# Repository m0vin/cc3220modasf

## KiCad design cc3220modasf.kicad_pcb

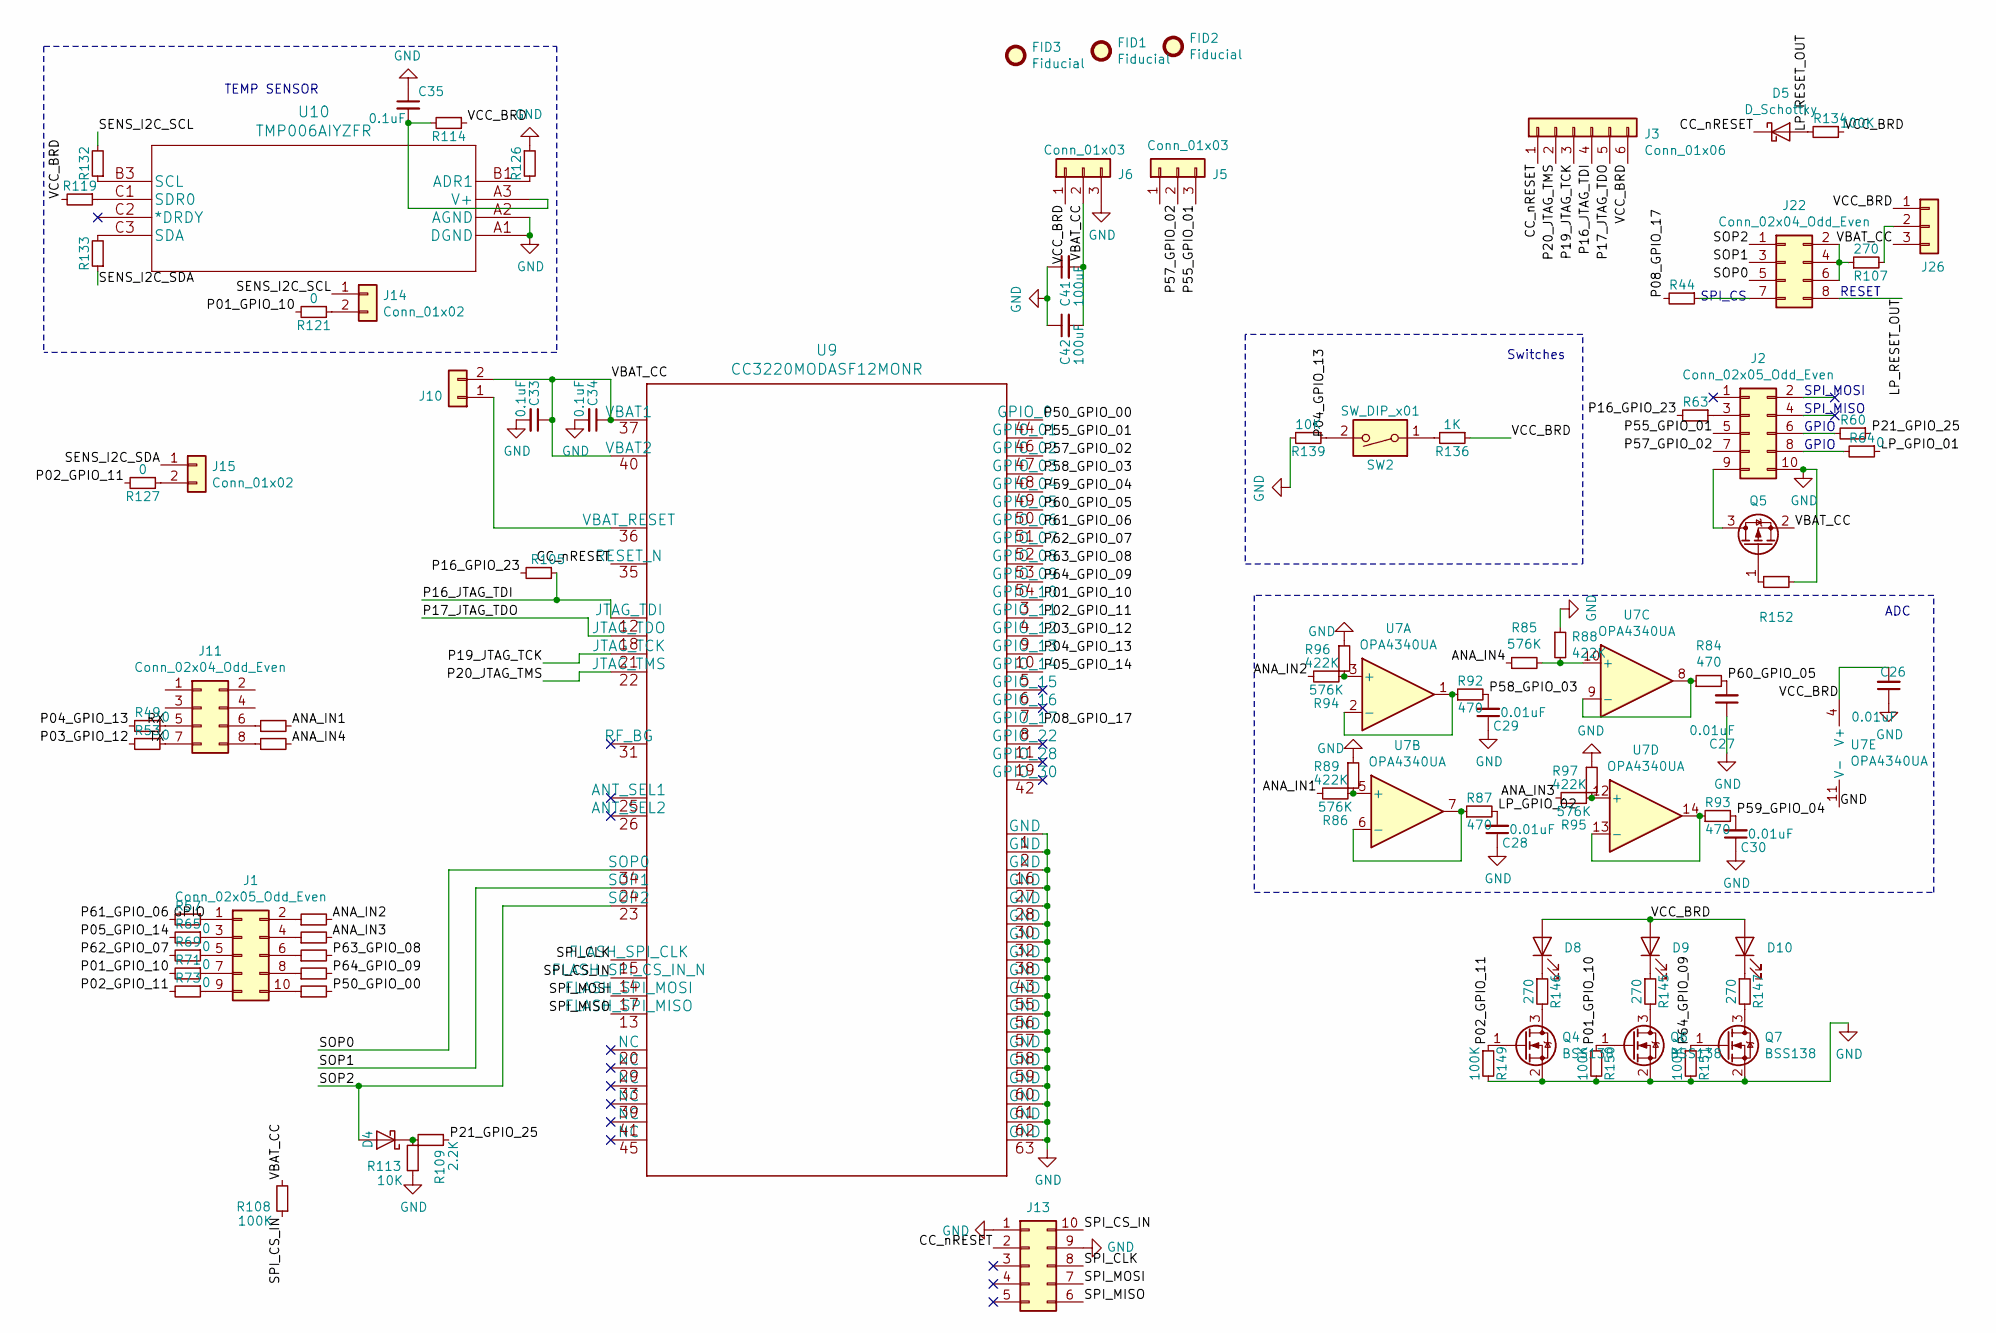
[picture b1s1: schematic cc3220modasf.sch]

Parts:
C26: 0.01uF; C_0402_1005Metric; MFG Part Num GRM155R61A103KA01D
C27, C28, C29, C30: 0.01uF; C_0402_1005Metric; MFG Part Num C1005X7R1C103K
C33, C34, C35: 0.1uF; C_0402_1005Metric; MFG Part Num GRM155R61A104KA01D
C41, C42: 100uF; C_1206_3216Metric; MFG Part Num GRM31CR60J107ME39L
D4, D5: D_Schottky; D_0603_1608Metric; MFG Part Num CD0603-B00340
D8: LED; LED_0603_1608Metric; MFG Part Num SML-LX0603GW-TR
D9: LED; LED_0603_1608Metric; MFG Part Num 150060YS75000
D10: LED; LED_0603_1608Metric; MFG Part Num SML-311UTT86
FID1, FID2, FID3: Fiducial; Fiducial_0.5mm_Mask1mm
J1, J2: Conn_02x05_Odd_Even; PinHeader_2x05_P2.54mm_Vertical
J3: Conn_01x06; PinSocket_1x06_P2.54mm_Vertical; MFG Part Num '61301021121
J5, J6: Conn_01x03; PinSocket_1x03_P2.54mm_Vertical
J10, J14, J15: Conn_01x02; PinHeader_1x02_P2.54mm_Vertical; MFG Part Num '61300211121
J11, J22: Conn_02x04_Odd_Even; PinHeader_2x04_P2.54mm_Vertical
J13: Conn_02x05_Counter_Clockwise; Tag-Connect_TC2050-IDC-NL_2x05_P1.27mm_Vertical_CC_SMD
J26: Conn_01x03; PinHeader_1x03_P2.54mm_Vertical; MFG Part Num '61300311121
Q4, Q6, Q7: BSS138; SOT-23; MFG Part Num BSS138
Q5: TP0610T; SuperSOT-3; MFG Part Num FDN358P
R44, R49, R50, R53, R54, R57, R58, R60, R62, R63, R64, R65, R66, R69, R71, R72, R73, R74, R105, R114, R119, R121, R126, R127, R132, R133, R152: 0; R_0402_1005Metric; MFG Part Num ERJ-2GE0R00X
R84, R87, R92, R93: 470; R_0402_1005Metric; MFG Part Num ERJ-2RKF4700X
R85, R86, R94, R95: 576K; R_0402_1005Metric; MFG Part Num CRCW0402576KFKED
R88, R89, R96, R97: 422K; R_0402_1005Metric; MFG Part Num CRCW0402422KFKED
R107: 270; R_0402_1005Metric; MFG Part Num ERJ-2GE0R00X
R108: 100K; R_0402_1005Metric; MFG Part Num CRCW0402100KDHEDP
R109: 2.2K; R_0402_1005Metric; MFG Part Num CRCW04022K20JNED
R113, R139: 10K; R_0402_1005Metric; MFG Part Num CRCW040210K0JNED
R134, R149, R150, R151: 100K; R_0402_1005Metric; MFG Part Num CRCW0402100KJNED
R136: 1K; R_0402_1005Metric; MFG Part Num CRCW04021K00JNED
R145, R146, R147: 270; R_0603_1608Metric; MFG Part Num CRCW0603270RJNEA
SW2: SW_DIP_x01; SW_Tactile_SPST_Angled_PTS645Vx31-2LFS; MFG Part Num MJTP1117
U7: OPA4340UA; TSSOP-14_4.4x5mm_P0.65mm; MFG Part Num OPA4342EA/250
U9: CC3220MODASF12MONR
U10: TMP006AIYZFR

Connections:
/ANA_IN1: R50.2, R86.2
/ANA_IN2: R58.2, R94.2
/ANA_IN3: R62.2, R95.2
/ANA_IN4: R54.2, R85.1
/CC_nRESET: D5.1 (K), J3.1, J13.2, U9.35 (RESET_N)
/GPIO: J1.1, R57.1
/LP_GPIO_02: C28.2, R87.2
/LP_RESET_OUT: D5.2 (A), J22.8, R134.2
/P01_GPIO_10: Q6.1 (G), R71.2, R121.2, R150.1, U9.3 (GPIO_10)
/P02_GPIO_11: Q4.1 (G), R73.2, R127.2, R149.1, U9.4 (GPIO_11)
/P03_GPIO_12: R53.2, U9.9 (GPIO_12)
/P04_GPIO_13: R49.2, R139.1, SW2.2, U9.10 (GPIO_13)
/P05_GPIO_14: R65.2, U9.5 (GPIO_14)
/P08_GPIO_17: R44.2, U9.8 (GPIO_17)
/P16_GPIO_23: R63.2, R105.2
/P16_JTAG_TDI: J3.4, R105.1, U9.12 (JTAG_TDI)
/P17_JTAG_TDO: J3.5, U9.18 (JTAG_TDO)
/P19_JTAG_TCK: J3.3, U9.21 (JTAG_TCK)
/P20_JTAG_TMS: J3.2, U9.22 (JTAG_TMS)
/P21_GPIO_25: R60.1, R109.1
/P50_GPIO_00: R74.2, U9.44 (GPIO_0)
/P55_GPIO_01: J2.5, J5.3, U9.46 (GPIO_01)
/P57_GPIO_02: J2.7, J5.2, U9.47 (GPIO_02)
/P58_GPIO_03: C29.2, R92.2, U9.48 (GPIO_03)
/P59_GPIO_04: C30.2, R93.2, U9.49 (GPIO_04)
/P60_GPIO_05: C27.2, R84.2, U9.50 (GPIO_05)
/P61_GPIO_06: R57.2, U9.51 (GPIO_06)
/P62_GPIO_07: R69.2, U9.52 (GPIO_07)
/P63_GPIO_08: R66.2, U9.53 (GPIO_08)
/P64_GPIO_09: Q7.1 (G), R72.2, R151.1, U9.54 (GPIO_09)
/RX: J11.5, R49.1
/SENS_I2C_SCL: J14.1, R132.2
/SENS_I2C_SDA: J15.1, R133.1
/SOP0: J22.5, U9.34 (SOP0)
/SOP1: J22.3, U9.24 (SOP1)
/SOP2: D4.2 (A), J22.1, U9.23 (SOP2)
/SPI_CLK: J13.8, U9.15 (FLASH_SPI_CLK)
/SPI_CS_IN: J13.10, R108.1, U9.14 (FLASH_SPI_CS_IN_N)
/SPI_MISO: J13.6, U9.13 (FLASH_SPI_MISO)
/SPI_MOSI: J13.7, U9.17 (FLASH_SPI_MOSI)
/TX: J11.7, R53.1
/VBAT_CC: C33.1, C34.1, C41.2, C42.2, J6.2, J10.2, J26.3, Q5.2 (S), R108.2, U9.37 (VBAT1), U9.40 (VBAT2)
/VCC_BRD: C26.2, D8.2 (A), D9.2 (A), D10.2 (A), J3.6, J6.1, J26.1, R114.1, R119.2, R134.1, R136.1, U7.4 (V+)
GND: C26.1, C27.1, C28.1, C29.1, C30.1, C33.2, C34.2, C35.1, C41.1, C42.1, J2.10, J6.3, J13.1, J13.9, Q4.2 (S), Q6.2 (S), Q7.2 (S), R88.1, R89.1, R96.1, R97.1, R113.1, R126.1, R139.2, R149.2, R150.2, R151.2, R152.1, U7.11 (V-), U9.1 (GND), U9.2 (GND), U9.16 (GND), U9.27 (GND), U9.28 (GND), U9.30 (GND), U9.32 (GND), U9.38 (GND), U9.43 (GND), U9.55 (GND), U9.56 (GND), U9.57 (GND), U9.58 (GND), U9.59 (GND), U9.60 (GND), U9.61 (GND), U9.62 (GND), U9.63 (GND), U10.A1 (DGND), U10.A2 (AGND)
unnamed: C35.2, R114.2, U10.A3 (V+)
unnamed: D4.1 (K), R109.2, R113.2
unnamed: D8.1 (K), R146.1
unnamed: D9.1 (K), R145.1
unnamed: D10.1 (K), R147.1
unnamed: J1.2, R58.1
unnamed: J1.3, R65.1
unnamed: J1.4, R62.1
unnamed: J1.5, R69.1
unnamed: J1.6, R66.1
unnamed: J1.7, R71.1
unnamed: J1.8, R72.1
unnamed: J1.9, R73.1
unnamed: J1.10, R74.1
unnamed: J2.3, R63.1
unnamed: J2.6, R60.2
unnamed: J2.8, R64.2
unnamed: J2.9, Q5.3 (D)
unnamed: J10.1, U9.36 (VBAT_RESET)
unnamed: J11.6, R50.1
unnamed: J11.8, R54.1
unnamed: J14.2, R121.1
unnamed: J15.2, R127.1
unnamed: J22.2, J22.4, J22.6, R107.1
unnamed: J22.7, R44.1
unnamed: J26.2, R107.2
unnamed: Q4.3 (D), R146.2
unnamed: Q5.1 (G), R152.2
unnamed: Q6.3 (D), R145.2
unnamed: Q7.3 (D), R147.2
unnamed: R84.1, U7.8, U7.9 (-)
unnamed: R85.2, R88.2, U7.10 (+)
unnamed: R86.1, R89.2, U7.5 (+)
unnamed: R87.1, U7.6 (-), U7.7
unnamed: R92.1, U7.1, U7.2 (-)
unnamed: R93.1, U7.13 (-), U7.14
unnamed: R94.1, R96.2, U7.3 (+)
unnamed: R95.1, R97.2, U7.12 (+)
unnamed: R119.1, U10.C1 (SDR0)
unnamed: R126.2, U10.B1 (ADR1)
unnamed: R132.1, U10.B3 (SCL)
unnamed: R133.2, U10.C3 (SDA)
unnamed: R136.2, SW2.1

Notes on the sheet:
Switches
TEMP SENSOR
ADC
GPIO
SPI_MISO
SPI_MOSI
RESET
SPI_CS

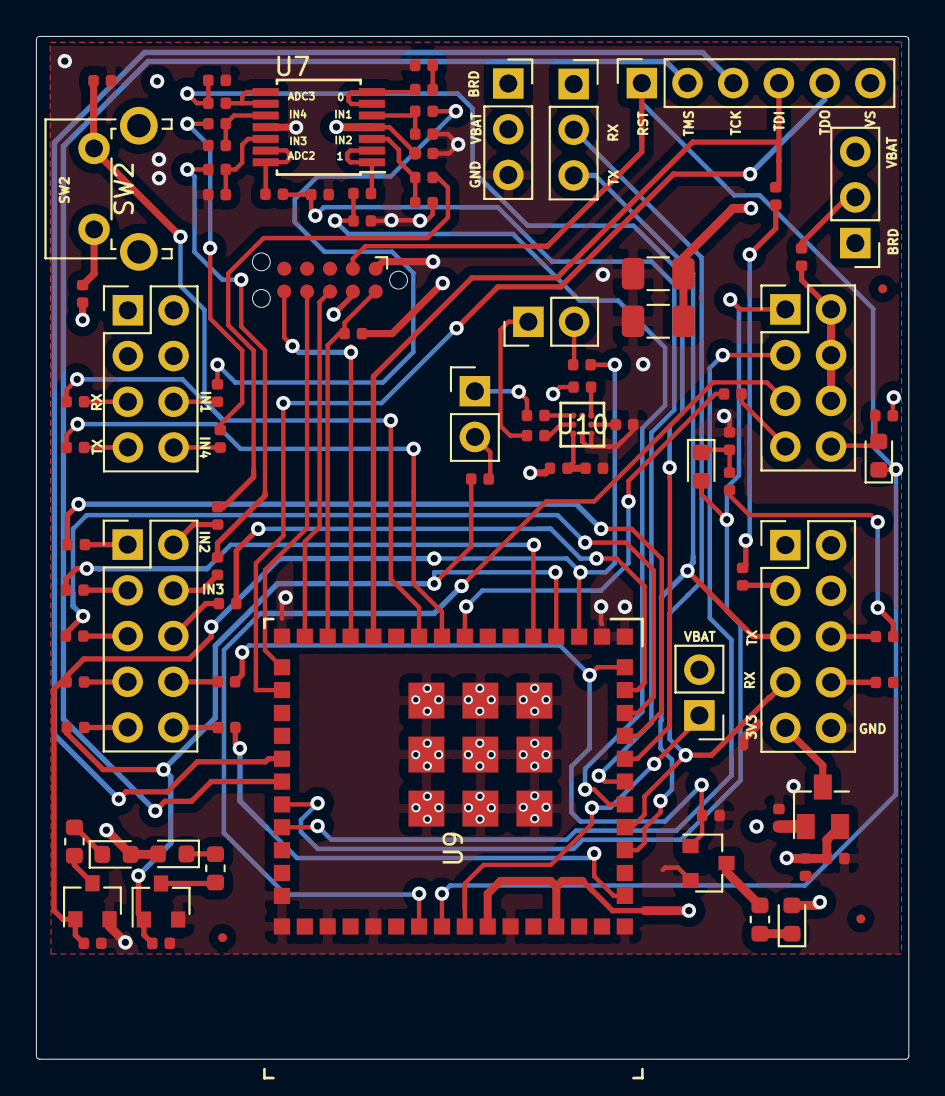
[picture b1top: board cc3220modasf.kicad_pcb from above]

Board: 4 copper layers, 48.5 x 56.8 mm, 90 parts (0 on the bottom side), 87 nets.

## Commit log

2020-10-06 Initial commit post newtech. ul_CC3220MODASF12MONR is modified from original - see notes
2020-10-07 Commit to record version prior to reducing board length to ~58mm
2020-10-12 Reduced board size to 49mmx57mm. Headers should now match pwrcon_1 commit from similar date

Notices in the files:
parts and their libraries:
Copyright 2016 Accelerated Designs. All rights reserved.
